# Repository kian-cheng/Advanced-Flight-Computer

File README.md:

# Advanced-Flight-Computer
A flight computer designed to be feature-rich and intuitive to use. Includes features for dual deployment, ignition, active flight stabilisation and data logging. 

Before this, I've only made a simpler flight computer on a perfboard that does data logging and manages ignition and ejection. So this is my opportunity to make something more advanced on a 4-layer PCB. 

## Features

- MCU: STM32H743VIT6
- Barometer: BMP 580
- IMU: ICM-45686
- GPS: ATGM336
- LORA: Ra-02
- USB-C
- Micro SD card reader
- 6 pyro channels
- 6 servo channels

## Schematic

## PCB layout

Designed using KiCad. PCB Image rendered in Blender.

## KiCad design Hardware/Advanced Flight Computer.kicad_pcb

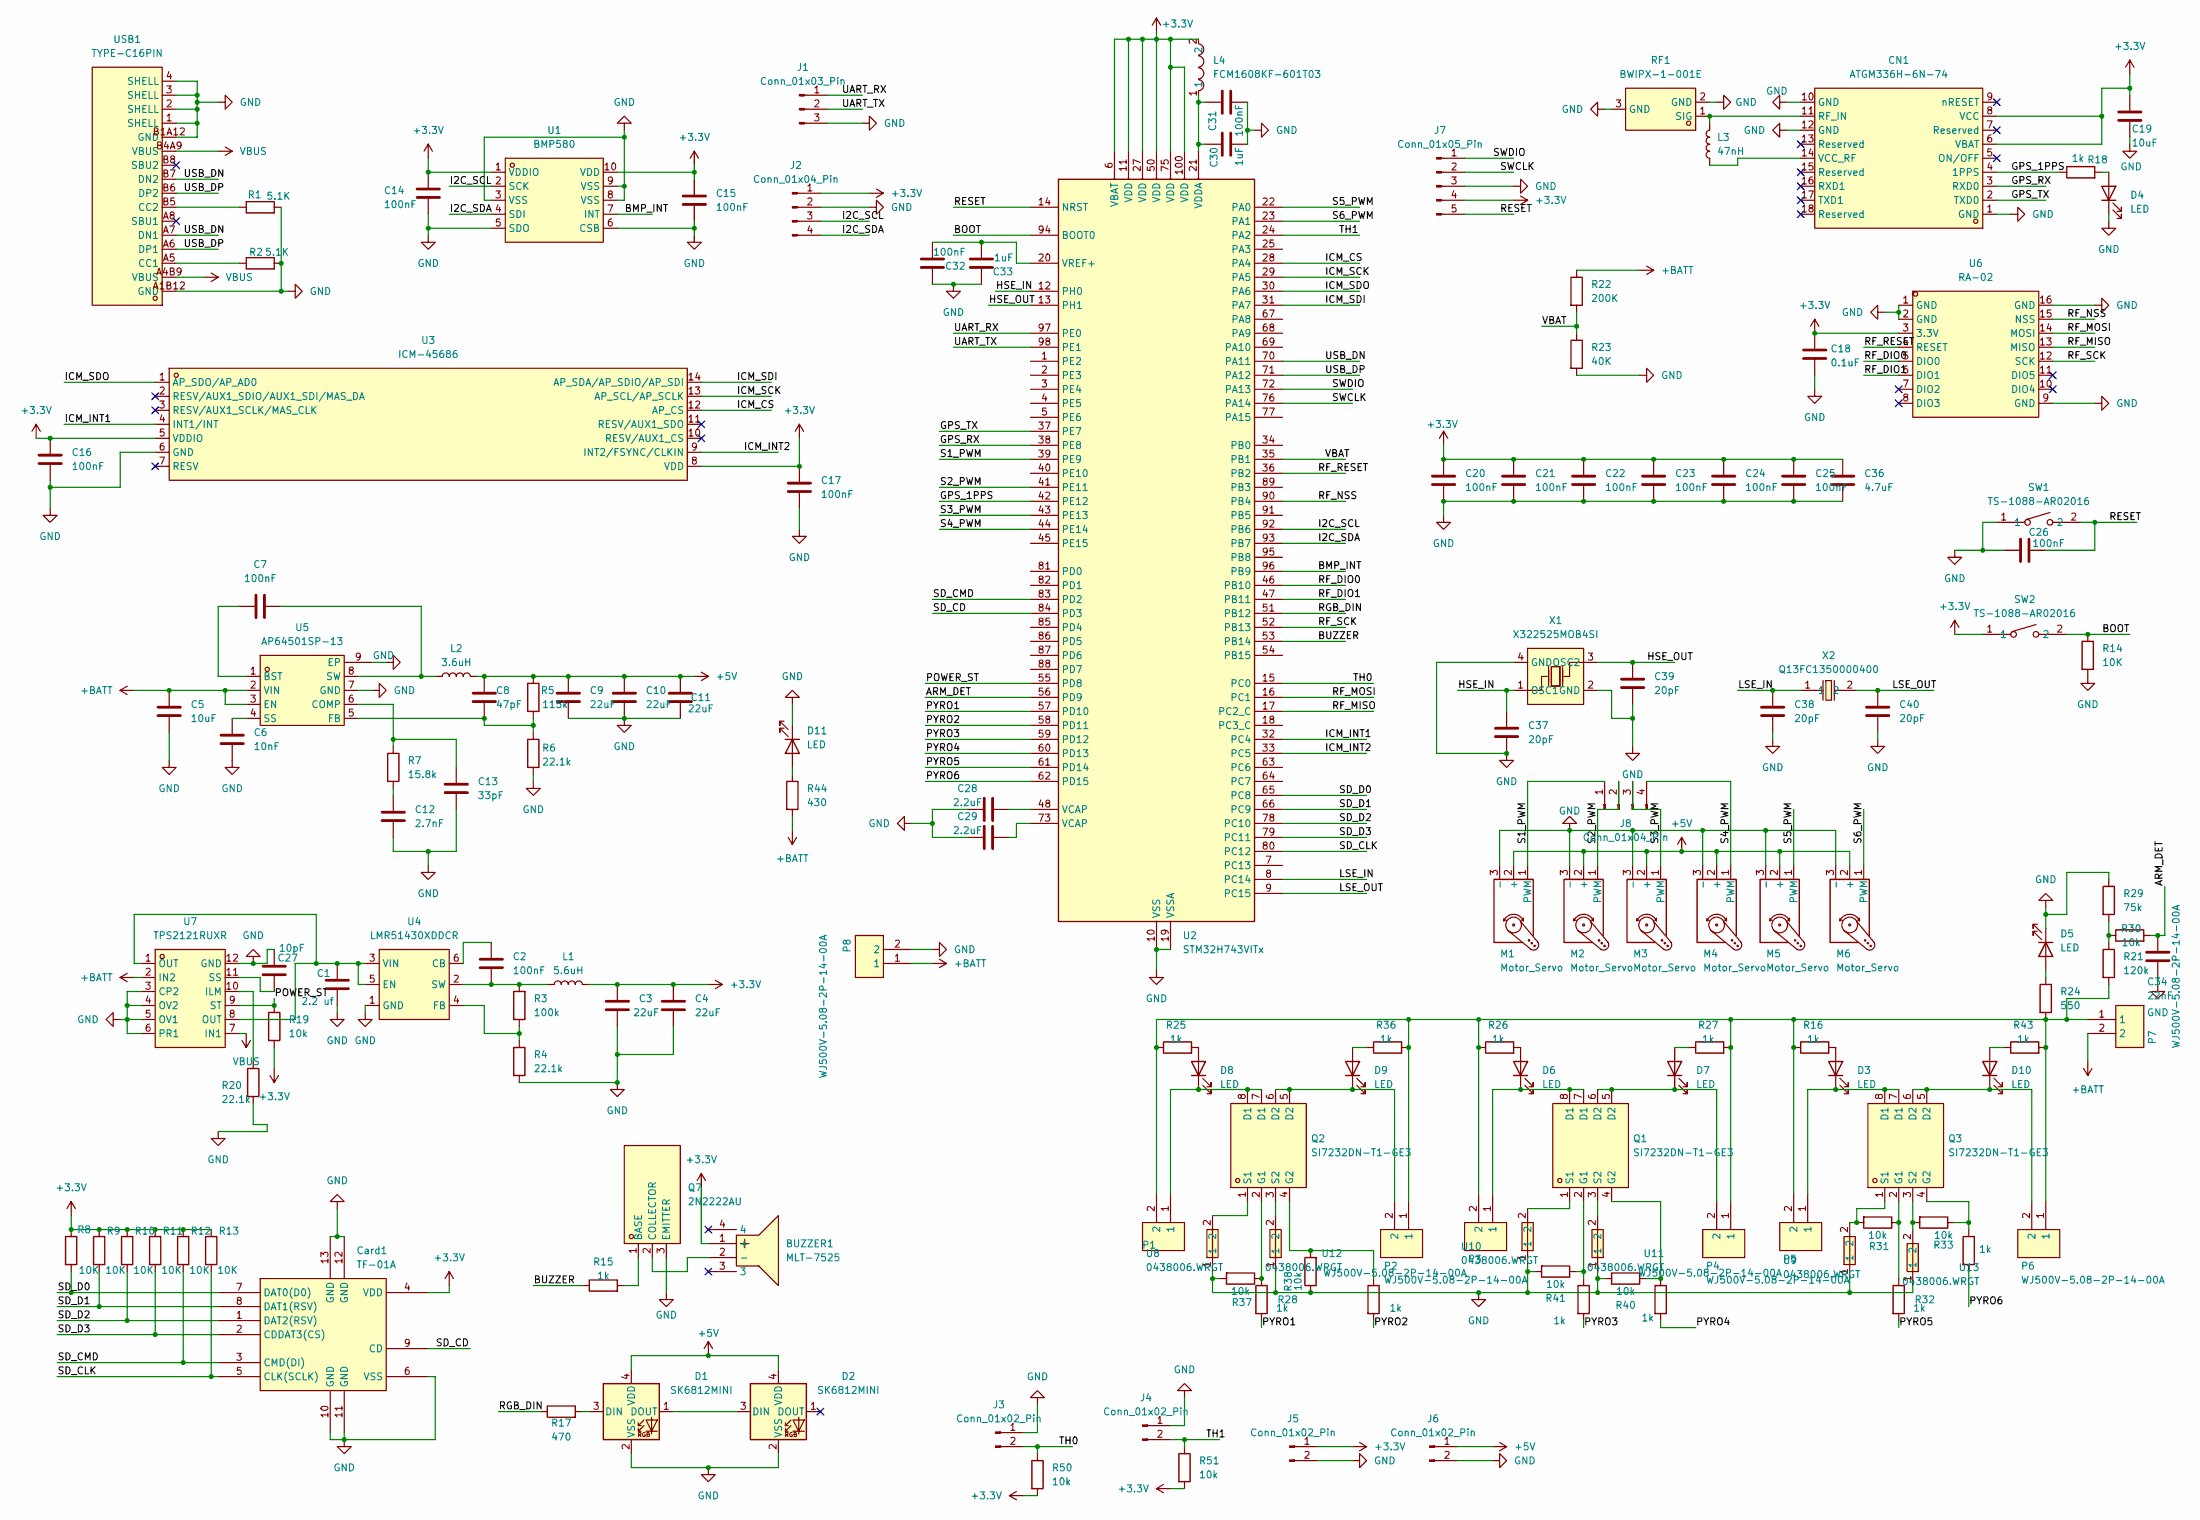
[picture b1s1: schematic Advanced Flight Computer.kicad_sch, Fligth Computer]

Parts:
BUZZER1: MLT-7525; BUZ-SMD_4P-L7.5-W7.5-P7.59-TL; LCSC Part C95299
C1: 2.2 uf; C_0805_2012Metric
C2, C7: 100nF; C_0603_1608Metric
C3, C4, C9, C10, C11: 22uF; C_0805_2012Metric
C5: 10uF; C_0805_2012Metric
C6: 10nF; C_0805_2012Metric
C8: 47pF; C_0805_2012Metric
C12: 2.7nF; C_0603_1608Metric
C13: 33pF; C_0603_1608Metric
C14, C15, C16, C17, C20, C21, C22, C23, C24, C25, C26, C31, C32: 100nF; C_0402_1005Metric
C18: 0.1uF; C_0402_1005Metric
C19: 10uF; C_0402_1005Metric
C27: 10pF; C_0402_1005Metric
C28, C29: 2.2uF; C_0402_1005Metric
C30, C33: 1uF; C_0402_1005Metric
C34: 22nF; C_0402_1005Metric
C36: 4.7uF; C_0402_1005Metric
C37, C38, C39, C40: 20pF; C_0402_1005Metric
CN1: ATGM336H-6N-74; COMM-SMD_18P-L10.1-W9.7-P1.1-TL_L76-LB; LCSC Part C5804601
Card1: TF-01A; TF-SMD_TF-01A; LCSC Part C91145
D1, D2: SK6812MINI; LED_SK6812MINI_PLCC4_3.5x3.5mm_P1.75mm
D3, D4, D6, D7, D8, D9, D10: LED; LED_0402_1005Metric
D5: LED; LED_0603_1608Metric
D11: LED; LED_0402_1005Metric; LCSC C130723
J1: Conn_01x03_Pin; PinHeader_1x03_P2.54mm_Vertical
J2: Conn_01x04_Pin; PinHeader_1x04_P2.54mm_Vertical
J3, J4: Conn_01x02_Pin; PinHeader_1x02_P2.54mm_Vertical
J5, J6: Conn_01x02_Pin; JST_XH_B2B-XH-AM_1x02_P2.50mm_Vertical; LCSC C158012
J7: Conn_01x05_Pin; PinHeader_1x05_P2.54mm_Vertical
J8: Conn_01x04_Pin; JST_XH_B4B-XH-AM_1x04_P2.50mm_Vertical
L1: 5.6uH; L_Bourns_SRP5030T; LCSC C46595886
L2: 3.6uH; L_Cenker_CKCS8040; LCSC C223037
L3: 47nH; L_0603_1608Metric_Pad1.05x0.95mm_HandSolder; LCSC C98076
L4: FCM1608KF-601T03; L0603; LCSC Part C141723
M1, M2, M3, M4, M5, M6: Motor_Servo; PinHeader_1x03_P2.54mm_Vertical
P1, P2, P3, P4, P5, P6, P7, P8: WJ500V-5.08-2P-14-00A; CONN-TH_2P-P5.00_WJ500V-5.08-2P; LCSC Part C8465
Q1, Q2, Q3: SI7232DN-T1-GE3; POWER-1212-8_L3.3-W3.3-P0.66-LS3.3-BL; LCSC Part C144854
Q7: 2N2222AU; SOT-89-3_L4.5-W2.4-P1.50-LS4.0-BR; LCSC Part C21714170
R1, R2: 5.1K; R_0402_1005Metric
R3: 100k; R_0402_1005Metric
R4, R6, R20: 22.1k; R_0402_1005Metric
R5: 115k; R_0402_1005Metric
R7: 15.8k; R_0402_1005Metric
R8, R9, R10, R11, R12, R13, R14: 10K; R_0402_1005Metric
R15, R16, R18, R25, R26, R27, R28, R32, R34, R35, R36, R39, R42, R43: 1k; R_0402_1005Metric
R17: 470; R_0402_1005Metric
R19, R30, R31, R33, R37, R38, R40, R41, R50, R51: 10k; R_0402_1005Metric
R21: 120k; R_0402_1005Metric
R22: 200K; R_0402_1005Metric
R23: 40K; R_0402_1005Metric
R24: 550; R_0402_1005Metric
R29: 75k; R_0402_1005Metric
R44: 430; R_0402_1005Metric
RF1: BWIPX-1-001E; IPEX-SMD_BWIPX-1-001E; LCSC Part C496552
SW1, SW2: TS-1088-AR02016; SW-SMD_L3.9-W3.0-P4.45; LCSC Part C720477
U1: BMP580; LGA-10_L2.0-W2.0-P0.50-TL_BMP580; LCSC Part C22391138
U2: STM32H743VITx; LQFP-100_14x14mm_P0.5mm
U3: ICM-45686; LGA-14_L3.0-W2.5-P0.50-TL; LCSC Part C22459454
U4: LMR51430XDDCR; SOT-23-6_L2.9-W1.6-P0.95-LS2.8-BL; LCSC Part C5185863
U5: AP64501SP-13; SOIC-8_L4.9-W3.9-P1.27-LS6.0-BL-EP-1; LCSC Part C2071517
U6: RA-02; WIRELM-SMD_RA-02-BL; LCSC Part C90039
U7: TPS2121RUXR; VQFN-HR-12_L2.5-W2.0-P0.50-BL; LCSC Part C485916
U8, U9, U10, U11, U12, U13: 0438006.WRGT; F0603; LCSC Part C206962
USB1: TYPE-C16PIN; USB-C-SMD_TYPE-C16PIN; LCSC Part C393939
X1: X322525MOB4SI; CRYSTAL-SMD_4P-L3.2-W2.5-BL; LCSC Part C9006
X2: Q13FC1350000400; FC-135R_L3.2-W1.5; LCSC Part C32346

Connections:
+3.3V: BUZZER1.1 (+), C3.1, C4.1, C14.1, C15.1, C16.1, C17.1, C18.1, C19.1, C20.1, C21.1, C22.1, C23.1, C24.1, C25.1, C36.1, CN1.6 (VBAT), CN1.8 (VCC), Card1.4 (VDD), J2.1, J5.1, J7.4, L1.2, L4.2, R8.1, R9.1, R10.1, R11.1, R12.1, R13.1, R19.2, R50.2, R51.2, SW2.1, U1.1 (VDDIO), U1.10 (VDD), U2.6 (VBAT), U2.11 (VDD), U2.27 (VDD), U2.50 (VDD), U2.75 (VDD), U2.100 (VDD), U3.5 (VDDIO), U3.8 (VDD), U6.3 (3.3V)
+5V: C8.1, C9.1, C10.1, C11.1, D1.4 (VDD), D2.4 (VDD), J6.1, L2.2, M1.2 (+), M2.2 (+), M3.2 (+), M4.2 (+), M5.2 (+), M6.2 (+), R5.1
+BATT: C5.1, P7.2, P8.1, R22.1, R44.2, U5.2 (VIN), U5.3 (EN), U7.2 (IN2)
/ARM_DET: C34.1, R30.2, U2.56 (PD9)
/BMP_INT: U1.7 (INT), U2.96 (PB9)
/BOOT: R14.1, SW2.2, U2.94 (BOOT0)
/BUZZER: R15.1, U2.53 (PB14)
/GPS_1PPS: CN1.4 (1PPS), R18.1, U2.42 (PE12)
/GPS_RX: CN1.3 (RXD0), U2.38 (PE8)
/GPS_TX: CN1.2 (TXD0), U2.37 (PE7)
/HSE_IN: C37.1, U2.12 (PH0), X1.1 (OSC1)
/HSE_OUT: C39.1, U2.13 (PH1), X1.3 (OSC2)
/I2C_SCL: J2.3, U1.2 (SCK), U2.92 (PB6)
/I2C_SDA: J2.4, U1.4 (SDI), U2.93 (PB7)
/ICM_CS: U2.28 (PA4), U3.12 (AP_CS)
/ICM_INT1: U2.32 (PC4), U3.4 (INT1/INT)
/ICM_INT2: U2.33 (PC5), U3.9 (INT2/FSYNC/CLKIN)
/ICM_SCK: U2.29 (PA5), U3.13 (AP_SCL/AP_SCLK)
/ICM_SDI: U2.31 (PA7), U3.14 (AP_SDA/AP_SDIO/AP_SDI)
/ICM_SDO: U2.30 (PA6), U3.1 (AP_SDO/AP_AD0)
/LSE_IN: C38.1, U2.8 (PC14), X2.1
/LSE_OUT: C40.1, U2.9 (PC15), X2.2
/POWER_ST: R19.1, U2.55 (PD8), U7.9 (ST)
/PYRO1: R28.2, U2.57 (PD10)
/PYRO2: R34.2, U2.58 (PD11)
/PYRO3: R35.2, U2.59 (PD12)
/PYRO4: R39.2, U2.60 (PD13)
/PYRO5: R32.2, U2.61 (PD14)
/PYRO6: R42.2, U2.62 (PD15)
/RESET: C26.2, J7.5, SW1.2, U2.14 (NRST)
/RF_DIO0: U2.46 (PB10), U6.5 (DIO0)
/RF_DIO1: U2.47 (PB11), U6.6 (DIO1)
/RF_MISO: U2.17 (PC2_C), U6.13 (MISO)
/RF_MOSI: U2.16 (PC1), U6.14 (MOSI)
/RF_NSS: U2.90 (PB4), U6.15 (NSS)
/RF_RESET: U2.36 (PB2), U6.4 (RESET)
/RF_SCK: U2.52 (PB13), U6.12 (SCK)
/RGB_DIN: R17.1, U2.51 (PB12)
/S1_PWM: J8.1, M1.1 (PWM), U2.39 (PE9)
/S2_PWM: J8.2, M2.1 (PWM), U2.41 (PE11)
/S3_PWM: J8.3, M3.1 (PWM), U2.43 (PE13)
/S4_PWM: J8.4, M4.1 (PWM), U2.44 (PE14)
/S5_PWM: M5.1 (PWM), U2.22 (PA0)
/S6_PWM: M6.1 (PWM), U2.23 (PA1)
/SD_CD: Card1.9 (CD), U2.84 (PD3)
/SD_CLK: Card1.5 (CLK(SCLK)), R13.2, U2.80 (PC12)
/SD_CMD: Card1.3 (CMD(DI)), R12.2, U2.83 (PD2)
/SD_D0: Card1.7 (DAT0(D0)), R8.2, U2.65 (PC8)
/SD_D1: Card1.8 (DAT1(RSV)), R9.2, U2.66 (PC9)
/SD_D2: Card1.1 (DAT2(RSV)), R10.2, U2.78 (PC10)
/SD_D3: Card1.2 (CDDAT3(CS)), R11.2, U2.79 (PC11)
/SWCLK: J7.2, U2.76 (PA14)
/SWDIO: J7.1, U2.72 (PA13)
/TH0: J3.2, R50.1, U2.15 (PC0)
/TH1: J4.2, R51.1, U2.24 (PA2)
/UART_RX: J1.1, U2.97 (PE0)
/UART_TX: J1.2, U2.98 (PE1)
/USB_DN: U2.70 (PA11), USB1.A7 (DN1), USB1.B7 (DN2)
/USB_DP: U2.71 (PA12), USB1.A6 (DP1), USB1.B6 (DP2)
/VBAT: R22.2, R23.1, U2.35 (PB1)
GND: C1.2, C3.2, C4.2, C5.2, C6.2, C9.2, C10.2, C11.2, C12.2, C13.2, C14.2, C15.2, C16.2, C17.2, C18.2, C19.2, C20.2, C21.2, C22.2, C23.2, C24.2, C25.2, C26.1, C27.1, C28.1, C29.1, C30.2, C31.2, C32.1, C33.1, C34.2, C36.2, C37.2, C38.2, C39.2, C40.2, CN1.1 (GND), CN1.10 (GND), CN1.12 (GND), Card1.6 (VSS), Card1.10 (GND), Card1.11 (GND), Card1.12 (GND), Card1.13 (GND), D1.2 (VSS), D2.2 (VSS), D4.1 (K), D5.1 (K), D11.1 (K), J1.3, J2.2, J3.1, J4.1, J5.2, J6.2, J7.3, M1.3 (-), M2.3 (-), M3.3 (-), M4.3 (-), M5.3 (-), M6.3 (-), P8.2, Q7.3 (EMITTER), R1.2, R2.2, R4.2, R6.2, R14.2, R20.2, R23.2, R29.1, R37.2, R38.1, R40.1, R41.2, RF1.2 (GND), RF1.3 (GND), SW1.1, U1.3 (VSS), U1.5 (SDO), U1.6 (CSB), U1.8 (VSS), U1.9 (VSS), U2.10 (VSS), U2.19 (VSSA), U2.26 (VSS), U2.49 (VSS), U2.74 (VSS), U2.99 (VSS), U3.6 (GND), U4.1 (GND), U5.7 (GND), U5.9 (EP), U6.1 (GND), U6.2 (GND), U6.9 (GND), U6.16 (GND), U7.3 (CP2), U7.4 (OV2), U7.5 (OV1), U7.6 (PR1), U7.12 (GND), U8.1, U9.1, U10.1, U11.1, U12.1, U13.1, USB1.1 (SHELL), USB1.2 (SHELL), USB1.3 (SHELL), USB1.4 (SHELL), USB1.A1B12 (GND), USB1.B1A12 (GND), X1.2 (GND), X1.4 (GND)
unnamed: BUZZER1.2 (-), Q7.2 (COLLECTOR)
unnamed: C12.1, R7.2
unnamed: C28.2, U2.48 (VCAP)
unnamed: C29.2, U2.73 (VCAP)
unnamed: CN1.11 (RF_IN), L3.2, RF1.1 (SIG)
unnamed: CN1.14 (VCC_RF), L3.1
unnamed: D1.3 (DIN), R17.2
unnamed: D1.1 (DOUT), D2.3 (DIN)
unnamed: D3.2 (A), R16.2
unnamed: D3.1 (K), P5.1, Q3.7 (D1), Q3.8 (D1)
unnamed: D4.2 (A), R18.2
unnamed: D5.2 (A), R24.1
unnamed: D6.2 (A), R26.2
unnamed: D6.1 (K), P3.1, Q1.7 (D1), Q1.8 (D1)
unnamed: D7.2 (A), R27.1
unnamed: D7.1 (K), P4.2, Q1.5 (D2), Q1.6 (D2)
unnamed: D8.2 (A), R25.2
unnamed: D8.1 (K), P1.1, Q2.7 (D1), Q2.8 (D1)
unnamed: D9.2 (A), R36.1
unnamed: D9.1 (K), P2.2, Q2.5 (D2), Q2.6 (D2)
unnamed: D10.2 (A), R43.1
unnamed: D10.1 (K), P6.2, Q3.5 (D2), Q3.6 (D2)
unnamed: D11.2 (A), R44.1
unnamed: P1.2, P2.1, P3.2, P4.1, P5.2, P6.1, P7.1, R16.1, R21.2, R24.2, R25.1, R26.1, R27.2, R36.2, R43.2
unnamed: Q1.2 (G1), R35.1, R41.1
unnamed: Q1.4 (G2), R39.1, R40.2
unnamed: Q1.1 (S1), U10.2
unnamed: Q1.3 (S2), U11.2
unnamed: Q2.2 (G1), R28.1, R37.1
unnamed: Q2.4 (G2), R34.1, R38.2
unnamed: Q2.1 (S1), U8.2
unnamed: Q2.3 (S2), U12.2
unnamed: Q3.2 (G1), R31.1, R32.1
unnamed: Q3.4 (G2), R33.1, R42.1
unnamed: Q3.1 (S1), R31.2, U9.2
unnamed: Q3.3 (S2), R33.2, U13.2
unnamed: Q7.1 (BASE), R15.2
unnamed: R21.1, R29.2, R30.1
unnamed: C30.1, C31.1, L4.1, U2.21 (VDDA)
unnamed: C32.2, C33.2, U2.20 (VREF+)
unnamed: C2.1, U4.6 (CB)
unnamed: C1.1, U4.3 (VIN), U4.5 (EN), U7.1 (OUT), U7.8 (OUT)
unnamed: R3.1, R4.1, U4.4 (FB)
unnamed: C2.2, L1.1, R3.2, U4.2 (SW)
unnamed: C7.1, U5.1 (BST)
unnamed: C13.1, R7.1, U5.6 (COMP)
unnamed: C8.2, R5.2, R6.1, U5.5 (FB)
unnamed: C6.1, U5.4 (SS)
unnamed: C7.2, L2.1, U5.8 (SW)
unnamed: R20.1, U7.10 (ILM)
unnamed: C27.2, U7.11 (SS)
unnamed: R2.1, USB1.A5 (CC1)
unnamed: R1.1, USB1.B5 (CC2)
VBUS: U7.7 (IN1), USB1.A4B9 (VBUS), USB1.B4A9 (VBUS)

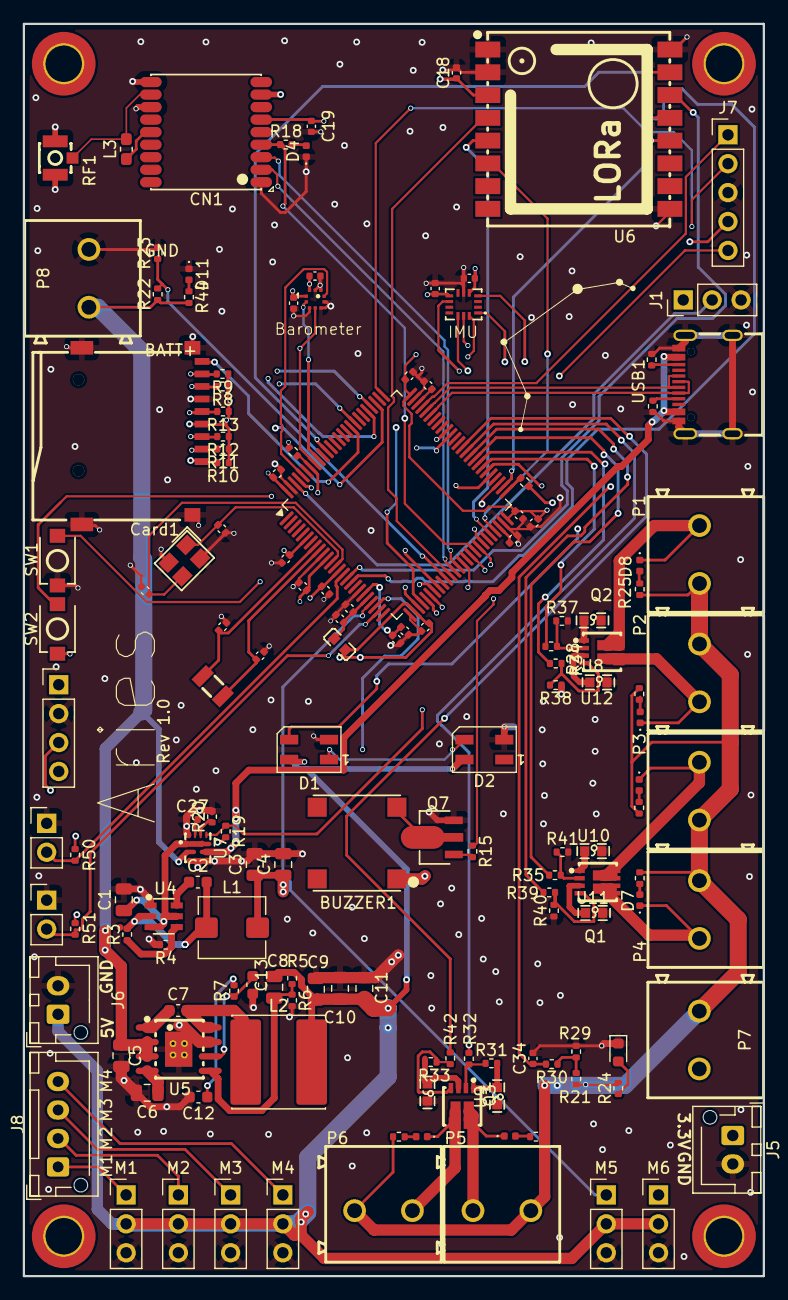
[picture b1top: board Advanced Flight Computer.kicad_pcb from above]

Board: 4 copper layers, 65.0 x 110.0 mm, 148 parts (0 on the bottom side), 115 nets.

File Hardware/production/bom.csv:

Designator,Footprint,Quantity,Value,LCSC Part #
BUZZER1,BUZ-SMD_4P-L7.5-W7.5-P7.59-TL,1,MLT-7525,C95299
C1,0805,1,2.2 uf,
"C10, C11, C3, C4, C9",0805,5,22uF,
C12,0603,1,2.7nF,
C13,0603,1,33pF,
"C14, C15, C16, C17, C20, C21, C22, C23, C24, C25, C26, C31, C32",0402,13,100nF,
C18,0402,1,0.1uF,
C19,0402,1,10uF,
"C2, C7",0603,2,100nF,
C27,0402,1,10pF,
"C28, C29",0402,2,2.2uF,
"C30, C33",0402,2,1uF,
C34,0402,1,22nF,
C36,0402,1,4.7uF,
"C37, C38, C39, C40",0402,4,20pF,
C5,0805,1,10uF,
C6,0805,1,10nF,
C8,0805,1,47pF,
CARD1,TF-SMD_TF-01A,1,TF-01A,C91145
CN1,COMM-SMD_18P-L10.1-W9.7-P1.1-TL_L76-LB,1,ATGM336H-6N-74,C5804601
"D1, D2",LED_SK6812MINI_PLCC4_3.5x3.5mm_P1.75mm,2,SK6812MINI,
"D10, D3, D6, D7, D8, D9",0402,6,LED,C25503345
D11,0402,1,LED,C130723
D4,0402,1,LED,C21260817
D5,0603,1,LED,C22371297
J1,PinHeader_1x03_P2.54mm_Vertical,1,Conn_01x03_Pin,
J2,PinHeader_1x04_P2.54mm_Vertical,1,Conn_01x04_Pin,
"J3, J4",PinHeader_1x02_P2.54mm_Vertical,2,Conn_01x02_Pin,
"J5, J6",JST_XH_B2B-XH-AM_1x02_P2.50mm_Vertical,2,Conn_01x02_Pin,C158012
J7,PinHeader_1x05_P2.54mm_Vertical,1,Conn_01x05_Pin,
J8,JST_XH_B4B-XH-AM_1x04_P2.50mm_Vertical,1,Conn_01x04_Pin,
L1,L_Bourns_SRP5030T,1,5.6uH,C46595886
L2,L_Cenker_CKCS8040,1,3.6uH,C223037
L3,0603,1,47nH,C98076
L4,L0603,1,FCM1608KF-601T03,C141723
"M1, M2, M3, M4, M5, M6",PinHeader_1x03_P2.54mm_Vertical,6,Motor_Servo,
"P1, P2, P3, P4, P5, P6, P7, P8",CONN-TH_2P-P5.00_WJ500V-5.08-2P,8,WJ500V-5.08-2P-14-00A,C8465
"Q1, Q2, Q3",POWER-1212-8_L3.3-W3.3-P0.66-LS3.3-BL,3,SI7232DN-T1-GE3,C144854
Q7,SOT-89-3_L4.5-W2.4-P1.50-LS4.0-BR,1,2N2222AU,C21714170
"R1, R2",0402,2,5.1K,
"R10, R11, R12, R13, R14, R19, R30, R31, R33, R37, R38, R40, R41, R50, R51, R8, R9",0402,17,10K,
"R15, R16, R18, R25, R26, R27, R28, R32, R34, R35, R36, R39, R42, R43",0402,14,1k,
R17,0402,1,470,
"R20, R4, R6",0402,3,22.1k,
R21,0402,1,120k,
R22,0402,1,200K,
R23,0402,1,40K,
R24,0402,1,550,
R29,0402,1,75k,
R3,0402,1,100k,
R44,0402,1,430,
R5,0402,1,115k,
R7,0402,1,15.8k,
RF1,IPEX-SMD_BWIPX-1-001E,1,BWIPX-1-001E,C496552
"SW1, SW2",SW-SMD_L3.9-W3.0-P4.45,2,TS-1088-AR02016,C720477
U1,LGA-10_L2.0-W2.0-P0.50-TL_BMP580,1,BMP580,C22391138
"U10, U11, U12, U13, U8, U9",F0603,6,0438006.WRGT,C206962
U2,LQFP-100_14x14mm_P0.5mm,1,STM32H743VITx,C114409
U3,LGA-14_L3.0-W2.5-P0.50-TL,1,ICM-45686,C22459454
U4,SOT-23-6_L2.9-W1.6-P0.95-LS2.8-BL,1,LMR51430XDDCR,C5185863
U5,SOIC-8_L4.9-W3.9-P1.27-LS6.0-BL-EP-1,1,AP64501SP-13,C2071517
U6,WIRELM-SMD_RA-02-BL,1,RA-02,C90039
U7,VQFN-HR-12_L2.5-W2.0-P0.50-BL,1,TPS2121RUXR,C485916
USB1,USB-C-SMD_TYPE-C16PIN,1,TYPE-C16PIN,C393939
X1,CRYSTAL-SMD_4P-L3.2-W2.5-BL,1,X322525MOB4SI,C9006
X2,FC-135R_L3.2-W1.5,1,Q13FC1350000400,C32346

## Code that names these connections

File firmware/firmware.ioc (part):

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Mcu.Name=STM32H743VITx
Mcu.Package=LQFP100
Mcu.UserName=STM32H743VITx
PA0.Signal=S_TIM2_CH1_ETR
PA1.Signal=S_TIM2_CH2
PA11.Mode=Device_Only
PA11.Signal=USB_OTG_FS_DM
PA12.Mode=Device_Only
PA12.Signal=USB_OTG_FS_DP
PA13\ (JTMS/SWDIO).Signal=DEBUG_JTMS-SWDIO
PA14\ (JTCK/SWCLK).Signal=DEBUG_JTCK-SWCLK
PA2.GPIOParameters=GPIO_Label
PA2.GPIO_Label=TH1
PA2.Signal=ADCx_INP14
PA4.Mode=NSS_Signal_Hard_Output
PA4.Signal=SPI1_NSS
PA5.Mode=Full_Duplex_Master
PA5.Signal=SPI1_SCK
PA6.Mode=Full_Duplex_Master
PA6.Signal=SPI1_MISO
PB1.GPIOParameters=GPIO_Label
PB1.GPIO_Label=VBAT
PB1.Signal=ADCx_INP5
PB10.GPIOParameters=GPIO_Label
PB10.GPIO_Label=RF_DIO0
PB10.Signal=GPXTI10
PB11.GPIOParameters=GPIO_Label
PB11.GPIO_Label=RF_DIO1
PB11.Signal=GPXTI11
PB12.GPIOParameters=GPIO_Label
PB12.GPIO_Label=RGB_DIN
PB12.Signal=GPIO_Output
PB13.Mode=Full_Duplex_Master
PB13.Signal=SPI2_SCK
PB14.GPIOParameters=GPIO_Label
PB14.GPIO_Label=BUZZER
PB14.Signal=S_TIM12_CH1
PB2.GPIOParameters=GPIO_Label
PB2.GPIO_Label=RF_RESET
PB2.Signal=GPIO_Input
PB4\ (NJTRST).Mode=NSS_Signal_Hard_Output
PB4\ (NJTRST).Signal=SPI2_NSS
PB6.Mode=I2C
PB6.Signal=I2C1_SCL
PB7.Mode=I2C
PB7.Signal=I2C1_SDA
PB9.GPIOParameters=GPIO_Label
PB9.GPIO_Label=BMP_INT
PB9.Signal=GPXTI9
PC0.GPIOParameters=GPIO_Label
PC0.GPIO_Label=TH0
PC0.Signal=ADCx_INP10
PC1.Mode=Full_Duplex_Master
PC1.Signal=SPI2_MOSI
PC10.Mode=SD_4_bits_Wide_bus
PC10.Signal=SDMMC1_D2
PC11.Mode=SD_4_bits_Wide_bus
PC11.Signal=SDMMC1_D3
PC12.Mode=SD_4_bits_Wide_bus
PC12.Signal=SDMMC1_CK
PC14-OSC32_IN\ (OSC32_IN).Mode=LSE-External-Oscillator
PC14-OSC32_IN\ (OSC32_IN).Signal=RCC_OSC32_IN
PC15-OSC32_OUT\ (OSC32_OUT).Mode=LSE-External-Oscillator
PC15-OSC32_OUT\ (OSC32_OUT).Signal=RCC_OSC32_OUT
PC2_C.Mode=Full_Duplex_Master
PC2_C.Signal=SPI2_MISO
PC4.GPIOParameters=GPIO_Label
PC4.GPIO_Label=ICM_INT1
PC4.Signal=GPXTI4
PC5.GPIOParameters=GPIO_Label
PC5.GPIO_Label=ICM_INT2
PC5.Signal=GPXTI5
PC8.Mode=SD_4_bits_Wide_bus
PC8.Signal=SDMMC1_D0
PC9.Mode=SD_4_bits_Wide_bus
PC9.Signal=SDMMC1_D1
PD10.Signal=GPIO_Output
PD11.Signal=GPIO_Output
PD12.Signal=GPIO_Output
PD13.Signal=GPIO_Output
PD14.Signal=GPIO_Output
PD15.Signal=GPIO_Output
PD2.Mode=SD_4_bits_Wide_bus
PD2.Signal=SDMMC1_CMD
PD3.GPIOParameters=GPIO_Label
PD3.GPIO_Label=SD_CD
PD3.Signal=GPIO_Input
PD7.Mode=Full_Duplex_Master
PD7.Signal=SPI1_MOSI
PD8.Signal=GPIO_Input
PD9.GPIOParameters=GPIO_Label
PD9.GPIO_Label=ARM_DET
PD9.Signal=GPIO_Input
PE0.Mode=Asynchronous
PE0.Signal=UART8_RX
PE1.Mode=Asynchronous
PE1.Signal=UART8_TX
PE11.Signal=S_TIM1_CH2
PE12.GPIOParameters=GPIO_Label
PE12.GPIO_Label=GPS_1PPS
PE12.Signal=GPXTI12
PE13.Signal=S_TIM1_CH3
PE14.Signal=S_TIM1_CH4
PE7.Mode=Asynchronous
PE7.Signal=UART7_RX
PE8.Mode=Asynchronous
PE8.Signal=UART7_TX
PE9.Signal=S_TIM1_CH1
PH0-OSC_IN\ (PH0).Mode=HSE-External-Oscillator
PH0-OSC_IN\ (PH0).Signal=RCC_OSC_IN
PH1-OSC_OUT\ (PH1).Mode=HSE-External-Oscillator
PH1-OSC_OUT\ (PH1).Signal=RCC_OSC_OUT
RCC.SYSCLKFreq_VALUE=64000000
board=custom

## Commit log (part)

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2025-12-01 Create folder and files for PCB
2025-12-01 started schematics and added libraries
2025-12-07 Added symbols, wired up some components in schematic.
2025-12-22 Update with latest changes
2025-12-28 Fix formatting of features list in README.md
2025-12-28 Improve README description for clarity and conciseness
2025-12-28 Update README with schematic and PCB layout images
    Added images for schematic and PCB layout.
2025-12-29 Update schematic image in README
2026-01-06 Update Flight Computer BOM with new links and items
2026-01-06 Update Flight Computer BOM with LCSC Shipping
    Added LCSC Shipping item to the BOM.
2026-02-07 Update to Render, PCB and Schematic
2026-02-07 Update to PCB
2026-02-07 Update images in README for schematic and PCB layout
2026-02-07 Update BOM
2026-02-08 Revise Flight Computer BOM with new components
    Updated item descriptions and added a new JST XH 4 pin entry.
2026-02-08 Update Flight Computer BOM with new items
    Added new item '1x05 pins' to the BOM with details.
2026-02-08 Revise Flight Computer BOM entries and links
    Updated the Flight Computer BOM with corrected item entries and links.
2026-02-18 Blender
2026-02-18 PCB fixes
2026-03-01 Update README with project background
    Added personal background and motivation for the project.
